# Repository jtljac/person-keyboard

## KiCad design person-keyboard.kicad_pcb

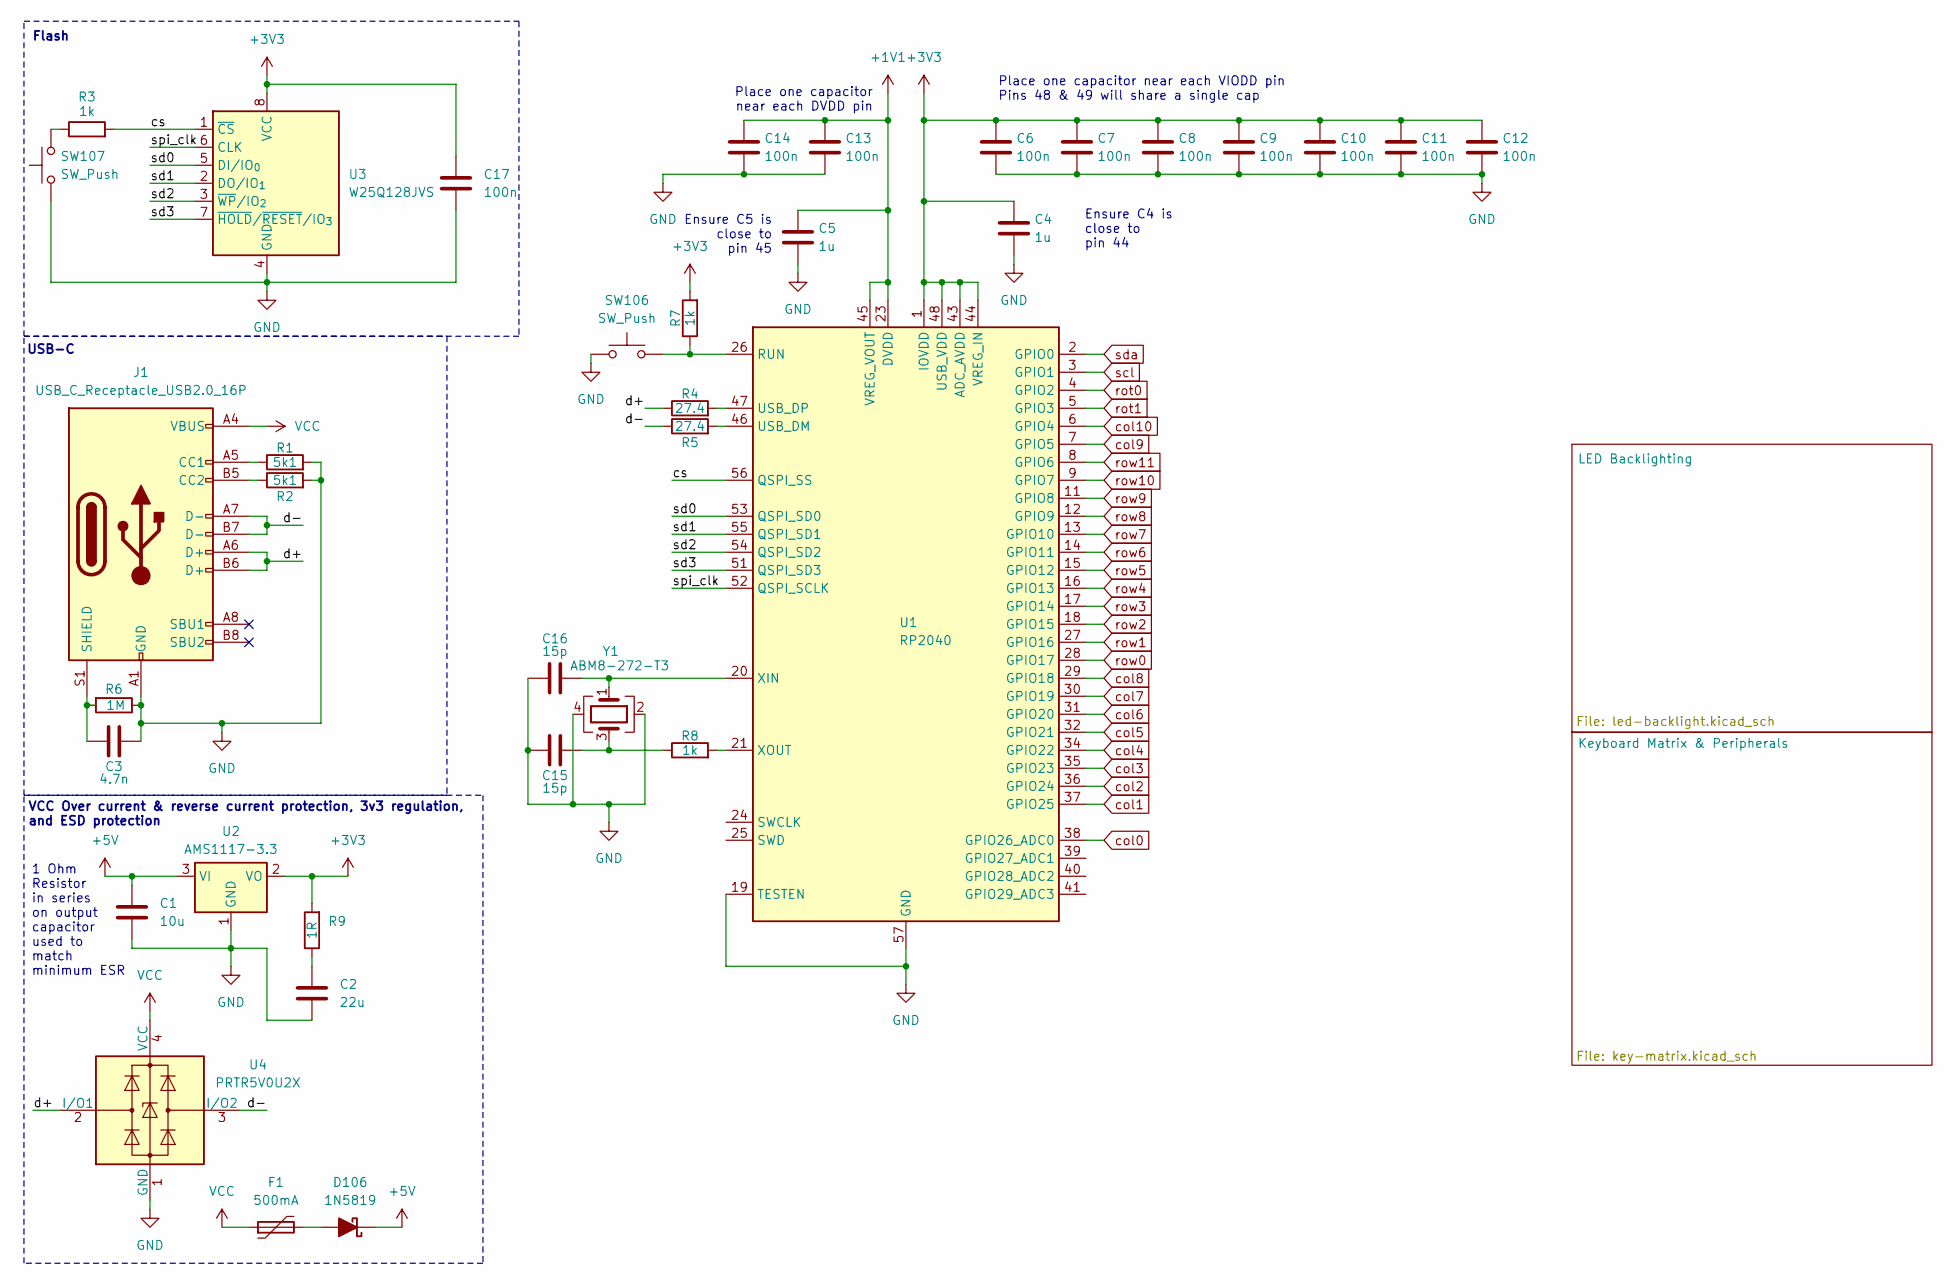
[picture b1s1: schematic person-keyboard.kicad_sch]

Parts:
C1: 10u; C_0805_2012Metric_Pad1.18x1.45mm_HandSolder
C2: 22u; C_0805_2012Metric_Pad1.18x1.45mm_HandSolder
C3: 4.7n; C_0805_2012Metric_Pad1.18x1.45mm_HandSolder
C4, C5: 1u; C_0402_1005Metric_Pad0.74x0.62mm_HandSolder
C6, C7, C8, C9, C10, C11, C12, C13, C14, C17: 100n; C_0402_1005Metric_Pad0.74x0.62mm_HandSolder
C15, C16: 15p; C_0402_1005Metric_Pad0.74x0.62mm_HandSolder
D106: 1N5819; D_SOD-123
F1: 500mA; Fuse_0805_2012Metric
J1: USB_C_Receptacle_USB2.0_16P; USB_C_Receptacle_GCT_USB4105-xx-A_16P_TopMnt_Horizontal
R1, R2: 5k1; R_0805_2012Metric_Pad1.20x1.40mm_HandSolder
R3: 1k; R_0805_2012Metric_Pad1.20x1.40mm_HandSolder
R4, R5: 27.4; R_0402_1005Metric_Pad0.72x0.64mm_HandSolder
R6: 1M; R_0805_2012Metric
R7, R8: 1k; R_0402_1005Metric_Pad0.72x0.64mm_HandSolder
R9: 1R; R_0805_2012Metric_Pad1.20x1.40mm_HandSolder
SW106, SW107: SW_Push; SW-SMD_L4.0-W2.9-LS5.0
U1: RP2040; QFN-56-1EP_7x7mm_P0.4mm_EP3.2x3.2mm_vias
U2: AMS1117-3.3; SOT-223-3_TabPin2
U3: W25Q128JVS; SOIC-8_5.3x5.3mm_P1.27mm
U4: PRTR5V0U2X; SOT-143
Y1: ABM8-272-T3; Crystal_SMD_3225-4Pin_3.2x2.5mm_HandSoldering

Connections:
+1V1: C5.1, C13.1, C14.1, U1.23 (DVDD), U1.45 (VREG_VOUT), U1.50 (DVDD)
+3V3: C4.1, C6.1, C7.1, C8.1, C9.1, C10.1, C11.1, C12.1, C17.1, R7.2, R9.2, U1.1 (IOVDD), U1.10 (IOVDD), U1.22 (IOVDD), U1.33 (IOVDD), U1.42 (IOVDD), U1.43 (ADC_AVDD), U1.44 (VREG_IN), U1.48 (USB_VDD), U1.49 (IOVDD), U2.2 (VO), U3.8 (VCC); also elsewhere on the board
+5V: C1.1, D106.1 (K), U2.3 (VI); also elsewhere on the board
/cs: R3.2, U1.56 (QSPI_SS), U3.1 (~CS)
/d+: J1.A6 (D+), J1.B6 (D+), R4.1, U4.2 (I/O1)
/d-: J1.A7 (D-), J1.B7 (D-), R5.1, U4.3 (I/O2)
/sd0: U1.53 (QSPI_SD0), U3.5 (DI/IO_{0})
/sd1: U1.55 (QSPI_SD1), U3.2 (DO/IO_{1})
/sd2: U1.54 (QSPI_SD2), U3.3 (~WP/IO_{2})
/sd3: U1.51 (QSPI_SD3), U3.7 (~HOLD/~RESET/IO_{3})
/spi_clk: U1.52 (QSPI_SCLK), U3.6 (CLK)
GND: C1.2, C2.2, C3.2, C4.2, C5.2, C6.2, C7.2, C8.2, C9.2, C10.2, C11.2, C12.2, C13.2, C14.2, C15.1, C16.1, C17.2, J1.A1 (GND), J1.A12 (GND), J1.B1 (GND), J1.B12 (GND), R1.2, R2.2, R6.1, SW106.1, SW107.1, U1.19 (TESTEN), U1.57 (GND), U2.1 (GND), U3.4 (GND), U4.1 (GND), Y1.2, Y1.4; also elsewhere on the board
unnamed: C2.1, R9.1
unnamed: C15.2, R8.1, Y1.3
unnamed: D106.2 (A), F1.2
unnamed: J1.A5 (CC1), R1.1
unnamed: J1.B5 (CC2), R2.1
unnamed: C3.1, J1.S1 (SHIELD), R6.2
unnamed: R3.1, SW107.2
unnamed: R7.1, SW106.2, U1.26 (RUN)
unnamed: R5.2, U1.46 (USB_DM)
unnamed: R4.2, U1.47 (USB_DP)
unnamed: C16.2, U1.20 (XIN), Y1.1
unnamed: R8.2, U1.21 (XOUT)
VCC: F1.1, J1.A4 (VBUS), J1.A9 (VBUS), J1.B4 (VBUS), J1.B9 (VBUS), U4.4 (VCC)
col0: U1.38 (GPIO26_ADC0); also elsewhere on the board
col1: U1.37 (GPIO25); also elsewhere on the board
col2: U1.36 (GPIO24); also elsewhere on the board
col3: U1.35 (GPIO23); also elsewhere on the board
col4: U1.34 (GPIO22); also elsewhere on the board
col5: U1.32 (GPIO21); also elsewhere on the board
col6: U1.31 (GPIO20); also elsewhere on the board
col7: U1.30 (GPIO19); also elsewhere on the board
col8: U1.29 (GPIO18); also elsewhere on the board
col9: U1.7 (GPIO5); also elsewhere on the board
col10: U1.6 (GPIO4); also elsewhere on the board
rot0: U1.4 (GPIO2); also elsewhere on the board
rot1: U1.5 (GPIO3); also elsewhere on the board
row0: U1.28 (GPIO17); also elsewhere on the board
row1: U1.27 (GPIO16); also elsewhere on the board
row2: U1.18 (GPIO15); also elsewhere on the board
row3: U1.17 (GPIO14); also elsewhere on the board
row4: U1.16 (GPIO13); also elsewhere on the board
row5: U1.15 (GPIO12); also elsewhere on the board
row6: U1.14 (GPIO11); also elsewhere on the board
row7: U1.13 (GPIO10); also elsewhere on the board
row8: U1.12 (GPIO9); also elsewhere on the board
row9: U1.11 (GPIO8); also elsewhere on the board
row10: U1.9 (GPIO7); also elsewhere on the board
row11: U1.8 (GPIO6); also elsewhere on the board
scl: U1.3 (GPIO1); also elsewhere on the board
sda: U1.2 (GPIO0); also elsewhere on the board

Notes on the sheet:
Place one capacitor near each DVDD pin
USB-C
VCC Over current & reverse current protection, 3v3 regulation, and ESD protection
1 Ohm Resistor in series on output capacitor used to match minimum ESR
Flash
Place one capacitor near each VIODD pin Pins 48 & 49 will share a single cap
Ensure C5 is close to pin 45
Ensure C4 is close to pin 44

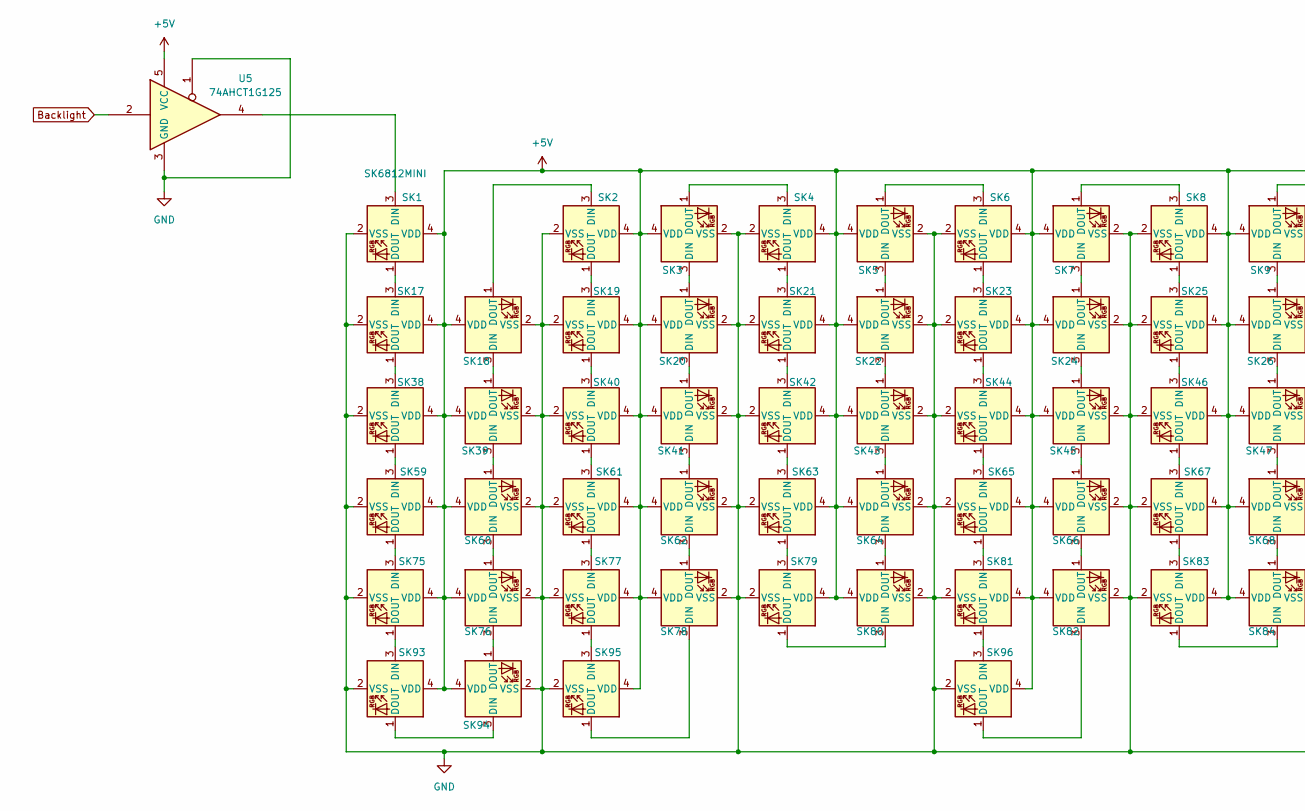
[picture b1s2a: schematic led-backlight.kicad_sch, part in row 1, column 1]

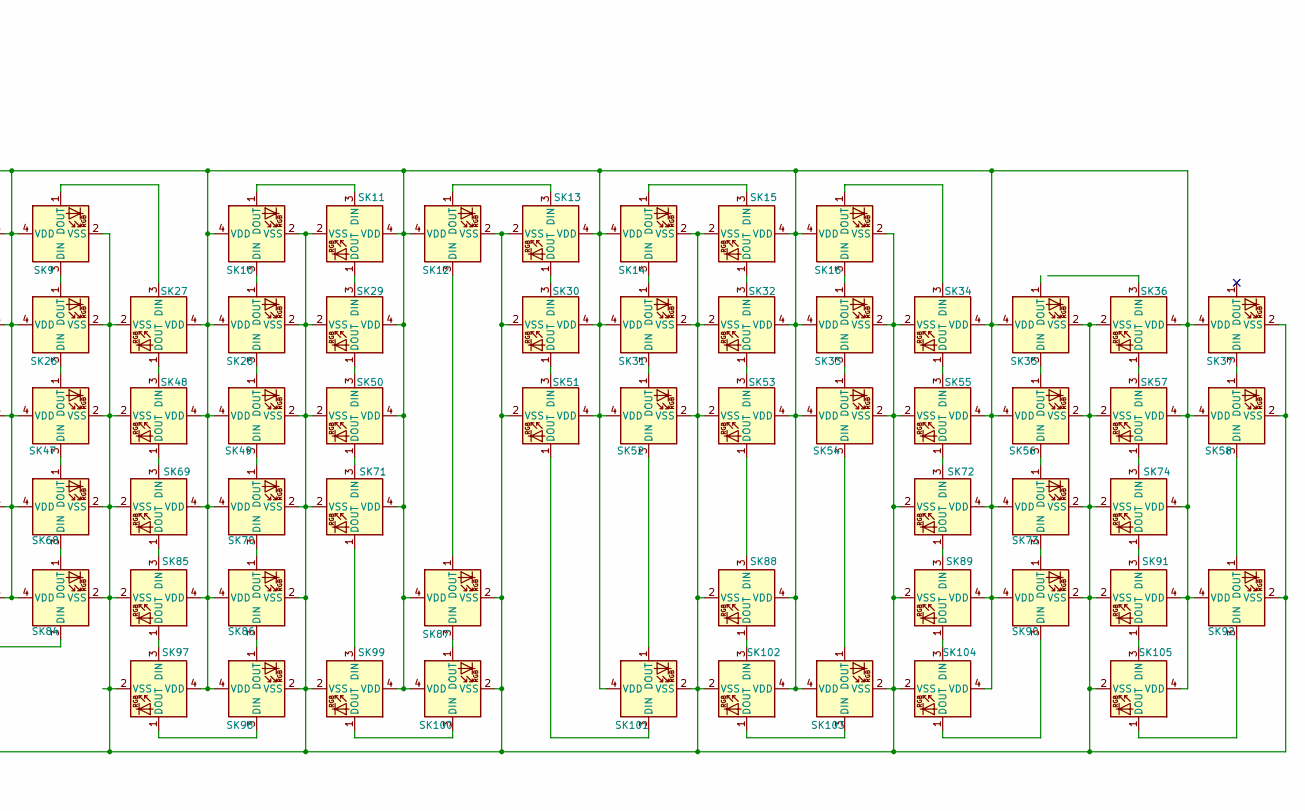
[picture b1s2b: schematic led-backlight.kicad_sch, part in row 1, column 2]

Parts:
SK1, SK2, SK3, SK4, SK5, SK6, SK7, SK8, SK9, SK10, SK11, SK12, SK13, SK14, SK15, SK16, SK17, SK18, SK19, SK20, SK21, SK22, SK23, SK24, SK25, SK26, SK27, SK28, SK29, SK30, SK31, SK32, SK33, SK34, SK35, SK36, SK37, SK38, SK39, SK40, SK41, SK42, SK43, SK44, SK45, SK46, SK47, SK48, SK49, SK50, SK51, SK52, SK53, SK54, SK55, SK56, SK57, SK58, SK59, SK60, SK61, SK62, SK63, SK64, SK65, SK66, SK67, SK68, SK69, SK70, SK71, SK72, SK73, SK74, SK75, SK76, SK77, SK78, SK79, SK80, SK81, SK82, SK83, SK84, SK85, SK86, SK87, SK88, SK89, SK90, SK91, SK92, SK93, SK94, SK95, SK96, SK97, SK98, SK99, SK100, SK101, SK102, SK103, SK104, SK105: SK6812MINI; SK6812-MINI-E
U5: 74AHCT1G125; SOT-23-5_HandSoldering

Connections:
+5V: SK1.4 (VDD), SK2.4 (VDD), SK3.4 (VDD), SK4.4 (VDD), SK5.4 (VDD), SK6.4 (VDD), SK7.4 (VDD), SK8.4 (VDD), SK9.4 (VDD), SK10.4 (VDD), SK11.4 (VDD), SK12.4 (VDD), SK13.4 (VDD), SK14.4 (VDD), SK15.4 (VDD), SK16.4 (VDD), SK17.4 (VDD), SK18.4 (VDD), SK19.4 (VDD), SK20.4 (VDD), SK21.4 (VDD), SK22.4 (VDD), SK23.4 (VDD), SK24.4 (VDD), SK25.4 (VDD), SK26.4 (VDD), SK27.4 (VDD), SK28.4 (VDD), SK29.4 (VDD), SK30.4 (VDD), SK31.4 (VDD), SK32.4 (VDD), SK33.4 (VDD), SK34.4 (VDD), SK35.4 (VDD), SK36.4 (VDD), SK37.4 (VDD), SK38.4 (VDD), SK39.4 (VDD), SK40.4 (VDD), SK41.4 (VDD), SK42.4 (VDD), SK43.4 (VDD), SK44.4 (VDD), SK45.4 (VDD), SK46.4 (VDD), SK47.4 (VDD), SK48.4 (VDD), SK49.4 (VDD), SK50.4 (VDD), SK51.4 (VDD), SK52.4 (VDD), SK53.4 (VDD), SK54.4 (VDD), SK55.4 (VDD), SK56.4 (VDD), SK57.4 (VDD), SK58.4 (VDD), SK59.4 (VDD), SK60.4 (VDD), SK61.4 (VDD), SK62.4 (VDD), SK63.4 (VDD), SK64.4 (VDD), SK65.4 (VDD), SK66.4 (VDD), SK67.4 (VDD), SK68.4 (VDD), SK69.4 (VDD), SK70.4 (VDD), SK71.4 (VDD), SK72.4 (VDD), SK73.4 (VDD), SK74.4 (VDD), SK75.4 (VDD), SK76.4 (VDD), SK77.4 (VDD), SK78.4 (VDD), SK79.4 (VDD), SK80.4 (VDD), SK81.4 (VDD), SK82.4 (VDD), SK83.4 (VDD), SK84.4 (VDD), SK85.4 (VDD), SK86.4 (VDD), SK87.4 (VDD), SK88.4 (VDD), SK89.4 (VDD), SK90.4 (VDD), SK91.4 (VDD), SK92.4 (VDD), SK93.4 (VDD), SK94.4 (VDD), SK95.4 (VDD), SK96.4 (VDD), SK97.4 (VDD), SK98.4 (VDD), SK99.4 (VDD), SK100.4 (VDD), SK101.4 (VDD), SK102.4 (VDD), SK103.4 (VDD), SK104.4 (VDD), SK105.4 (VDD), U5.5 (VCC); also elsewhere on the board
Backlight: U5.2
GND: SK1.2 (VSS), SK2.2 (VSS), SK3.2 (VSS), SK4.2 (VSS), SK5.2 (VSS), SK6.2 (VSS), SK7.2 (VSS), SK8.2 (VSS), SK9.2 (VSS), SK10.2 (VSS), SK11.2 (VSS), SK12.2 (VSS), SK13.2 (VSS), SK14.2 (VSS), SK15.2 (VSS), SK16.2 (VSS), SK17.2 (VSS), SK18.2 (VSS), SK19.2 (VSS), SK20.2 (VSS), SK21.2 (VSS), SK22.2 (VSS), SK23.2 (VSS), SK24.2 (VSS), SK25.2 (VSS), SK26.2 (VSS), SK27.2 (VSS), SK28.2 (VSS), SK29.2 (VSS), SK30.2 (VSS), SK31.2 (VSS), SK32.2 (VSS), SK33.2 (VSS), SK34.2 (VSS), SK35.2 (VSS), SK36.2 (VSS), SK37.2 (VSS), SK38.2 (VSS), SK39.2 (VSS), SK40.2 (VSS), SK41.2 (VSS), SK42.2 (VSS), SK43.2 (VSS), SK44.2 (VSS), SK45.2 (VSS), SK46.2 (VSS), SK47.2 (VSS), SK48.2 (VSS), SK49.2 (VSS), SK50.2 (VSS), SK51.2 (VSS), SK52.2 (VSS), SK53.2 (VSS), SK54.2 (VSS), SK55.2 (VSS), SK56.2 (VSS), SK57.2 (VSS), SK58.2 (VSS), SK59.2 (VSS), SK60.2 (VSS), SK61.2 (VSS), SK62.2 (VSS), SK63.2 (VSS), SK64.2 (VSS), SK65.2 (VSS), SK66.2 (VSS), SK67.2 (VSS), SK68.2 (VSS), SK69.2 (VSS), SK70.2 (VSS), SK71.2 (VSS), SK72.2 (VSS), SK73.2 (VSS), SK74.2 (VSS), SK75.2 (VSS), SK76.2 (VSS), SK77.2 (VSS), SK78.2 (VSS), SK79.2 (VSS), SK80.2 (VSS), SK81.2 (VSS), SK82.2 (VSS), SK83.2 (VSS), SK84.2 (VSS), SK85.2 (VSS), SK86.2 (VSS), SK87.2 (VSS), SK88.2 (VSS), SK89.2 (VSS), SK90.2 (VSS), SK91.2 (VSS), SK92.2 (VSS), SK93.2 (VSS), SK94.2 (VSS), SK95.2 (VSS), SK96.2 (VSS), SK97.2 (VSS), SK98.2 (VSS), SK99.2 (VSS), SK100.2 (VSS), SK101.2 (VSS), SK102.2 (VSS), SK103.2 (VSS), SK104.2 (VSS), SK105.2 (VSS), U5.1, U5.3 (GND); also elsewhere on the board
unnamed: SK1.3 (DIN), U5.4
unnamed: SK1.1 (DOUT), SK17.3 (DIN)
unnamed: SK3.1 (DOUT), SK4.3 (DIN)
unnamed: SK5.1 (DOUT), SK6.3 (DIN)
unnamed: SK7.1 (DOUT), SK8.3 (DIN)
unnamed: SK10.3 (DIN), SK28.1 (DOUT)
unnamed: SK10.1 (DOUT), SK11.3 (DIN)
unnamed: SK11.1 (DOUT), SK29.3 (DIN)
unnamed: SK12.3 (DIN), SK87.1 (DOUT)
unnamed: SK12.1 (DOUT), SK13.3 (DIN)
unnamed: SK13.1 (DOUT), SK30.3 (DIN)
unnamed: SK14.3 (DIN), SK31.1 (DOUT)
unnamed: SK14.1 (DOUT), SK15.3 (DIN)
unnamed: SK15.1 (DOUT), SK32.3 (DIN)
unnamed: SK16.3 (DIN), SK33.1 (DOUT)
unnamed: SK16.1 (DOUT), SK34.3 (DIN)
unnamed: SK17.1 (DOUT), SK38.3 (DIN)
unnamed: SK18.3 (DIN), SK39.1 (DOUT)
unnamed: SK2.3 (DIN), SK18.1 (DOUT)
unnamed: SK2.1 (DOUT), SK19.3 (DIN)
unnamed: SK19.1 (DOUT), SK40.3 (DIN)
unnamed: SK20.3 (DIN), SK41.1 (DOUT)
unnamed: SK3.3 (DIN), SK20.1 (DOUT)
unnamed: SK4.1 (DOUT), SK21.3 (DIN)
unnamed: SK21.1 (DOUT), SK42.3 (DIN)
unnamed: SK22.3 (DIN), SK43.1 (DOUT)
unnamed: SK5.3 (DIN), SK22.1 (DOUT)
unnamed: SK6.1 (DOUT), SK23.3 (DIN)
unnamed: SK23.1 (DOUT), SK44.3 (DIN)
unnamed: SK24.3 (DIN), SK45.1 (DOUT)
unnamed: SK7.3 (DIN), SK24.1 (DOUT)
unnamed: SK8.1 (DOUT), SK25.3 (DIN)
unnamed: SK25.1 (DOUT), SK46.3 (DIN)
unnamed: SK26.3 (DIN), SK47.1 (DOUT)
unnamed: SK9.3 (DIN), SK26.1 (DOUT)
unnamed: SK9.1 (DOUT), SK27.3 (DIN)
unnamed: SK27.1 (DOUT), SK48.3 (DIN)
unnamed: SK28.3 (DIN), SK49.1 (DOUT)
unnamed: SK29.1 (DOUT), SK50.3 (DIN)
unnamed: SK30.1 (DOUT), SK51.3 (DIN)
unnamed: SK31.3 (DIN), SK52.1 (DOUT)
unnamed: SK32.1 (DOUT), SK53.3 (DIN)
unnamed: SK33.3 (DIN), SK54.1 (DOUT)
unnamed: SK34.1 (DOUT), SK55.3 (DIN)
unnamed: SK35.3 (DIN), SK56.1 (DOUT)
unnamed: SK36.1 (DOUT), SK57.3 (DIN)
unnamed: SK37.3 (DIN), SK58.1 (DOUT)
unnamed: SK38.1 (DOUT), SK59.3 (DIN)
unnamed: SK39.3 (DIN), SK60.1 (DOUT)
unnamed: SK40.1 (DOUT), SK61.3 (DIN)
unnamed: SK41.3 (DIN), SK62.1 (DOUT)
unnamed: SK42.1 (DOUT), SK63.3 (DIN)
unnamed: SK43.3 (DIN), SK64.1 (DOUT)
unnamed: SK44.1 (DOUT), SK65.3 (DIN)
unnamed: SK45.3 (DIN), SK66.1 (DOUT)
unnamed: SK46.1 (DOUT), SK67.3 (DIN)
unnamed: SK47.3 (DIN), SK68.1 (DOUT)
unnamed: SK48.1 (DOUT), SK69.3 (DIN)
unnamed: SK49.3 (DIN), SK70.1 (DOUT)
unnamed: SK50.1 (DOUT), SK71.3 (DIN)
unnamed: SK53.1 (DOUT), SK88.3 (DIN)
unnamed: SK55.1 (DOUT), SK72.3 (DIN)
unnamed: SK56.3 (DIN), SK73.1 (DOUT)
unnamed: SK57.1 (DOUT), SK74.3 (DIN)
unnamed: SK58.3 (DIN), SK92.1 (DOUT)
unnamed: SK59.1 (DOUT), SK75.3 (DIN)
unnamed: SK60.3 (DIN), SK76.1 (DOUT)
unnamed: SK61.1 (DOUT), SK77.3 (DIN)
unnamed: SK62.3 (DIN), SK78.1 (DOUT)
unnamed: SK63.1 (DOUT), SK79.3 (DIN)
unnamed: SK64.3 (DIN), SK80.1 (DOUT)
unnamed: SK65.1 (DOUT), SK81.3 (DIN)
unnamed: SK66.3 (DIN), SK82.1 (DOUT)
unnamed: SK67.1 (DOUT), SK83.3 (DIN)
unnamed: SK68.3 (DIN), SK84.1 (DOUT)
unnamed: SK69.1 (DOUT), SK85.3 (DIN)
unnamed: SK70.3 (DIN), SK86.1 (DOUT)
unnamed: SK71.1 (DOUT), SK99.3 (DIN)
unnamed: SK72.1 (DOUT), SK89.3 (DIN)
unnamed: SK73.3 (DIN), SK90.1 (DOUT)
unnamed: SK74.1 (DOUT), SK91.3 (DIN)
unnamed: SK75.1 (DOUT), SK93.3 (DIN)
unnamed: SK76.3 (DIN), SK94.1 (DOUT)
unnamed: SK77.1 (DOUT), SK95.3 (DIN)
unnamed: SK78.3 (DIN), SK95.1 (DOUT)
unnamed: SK79.1 (DOUT), SK80.3 (DIN)
unnamed: SK81.1 (DOUT), SK96.3 (DIN)
unnamed: SK82.3 (DIN), SK96.1 (DOUT)
unnamed: SK83.1 (DOUT), SK84.3 (DIN)
unnamed: SK85.1 (DOUT), SK97.3 (DIN)
unnamed: SK86.3 (DIN), SK98.1 (DOUT)
unnamed: SK93.1 (DOUT), SK94.3 (DIN)
unnamed: SK97.1 (DOUT), SK98.3 (DIN)
unnamed: SK99.1 (DOUT), SK100.3 (DIN)
unnamed: SK87.3 (DIN), SK100.1 (DOUT)
unnamed: SK51.1 (DOUT), SK101.3 (DIN)
unnamed: SK52.3 (DIN), SK101.1 (DOUT)
unnamed: SK88.1 (DOUT), SK102.3 (DIN)
unnamed: SK102.1 (DOUT), SK103.3 (DIN)
unnamed: SK54.3 (DIN), SK103.1 (DOUT)
unnamed: SK89.1 (DOUT), SK104.3 (DIN)
unnamed: SK90.3 (DIN), SK104.1 (DOUT)
unnamed: SK91.1 (DOUT), SK105.3 (DIN)
unnamed: SK92.3 (DIN), SK105.1 (DOUT)

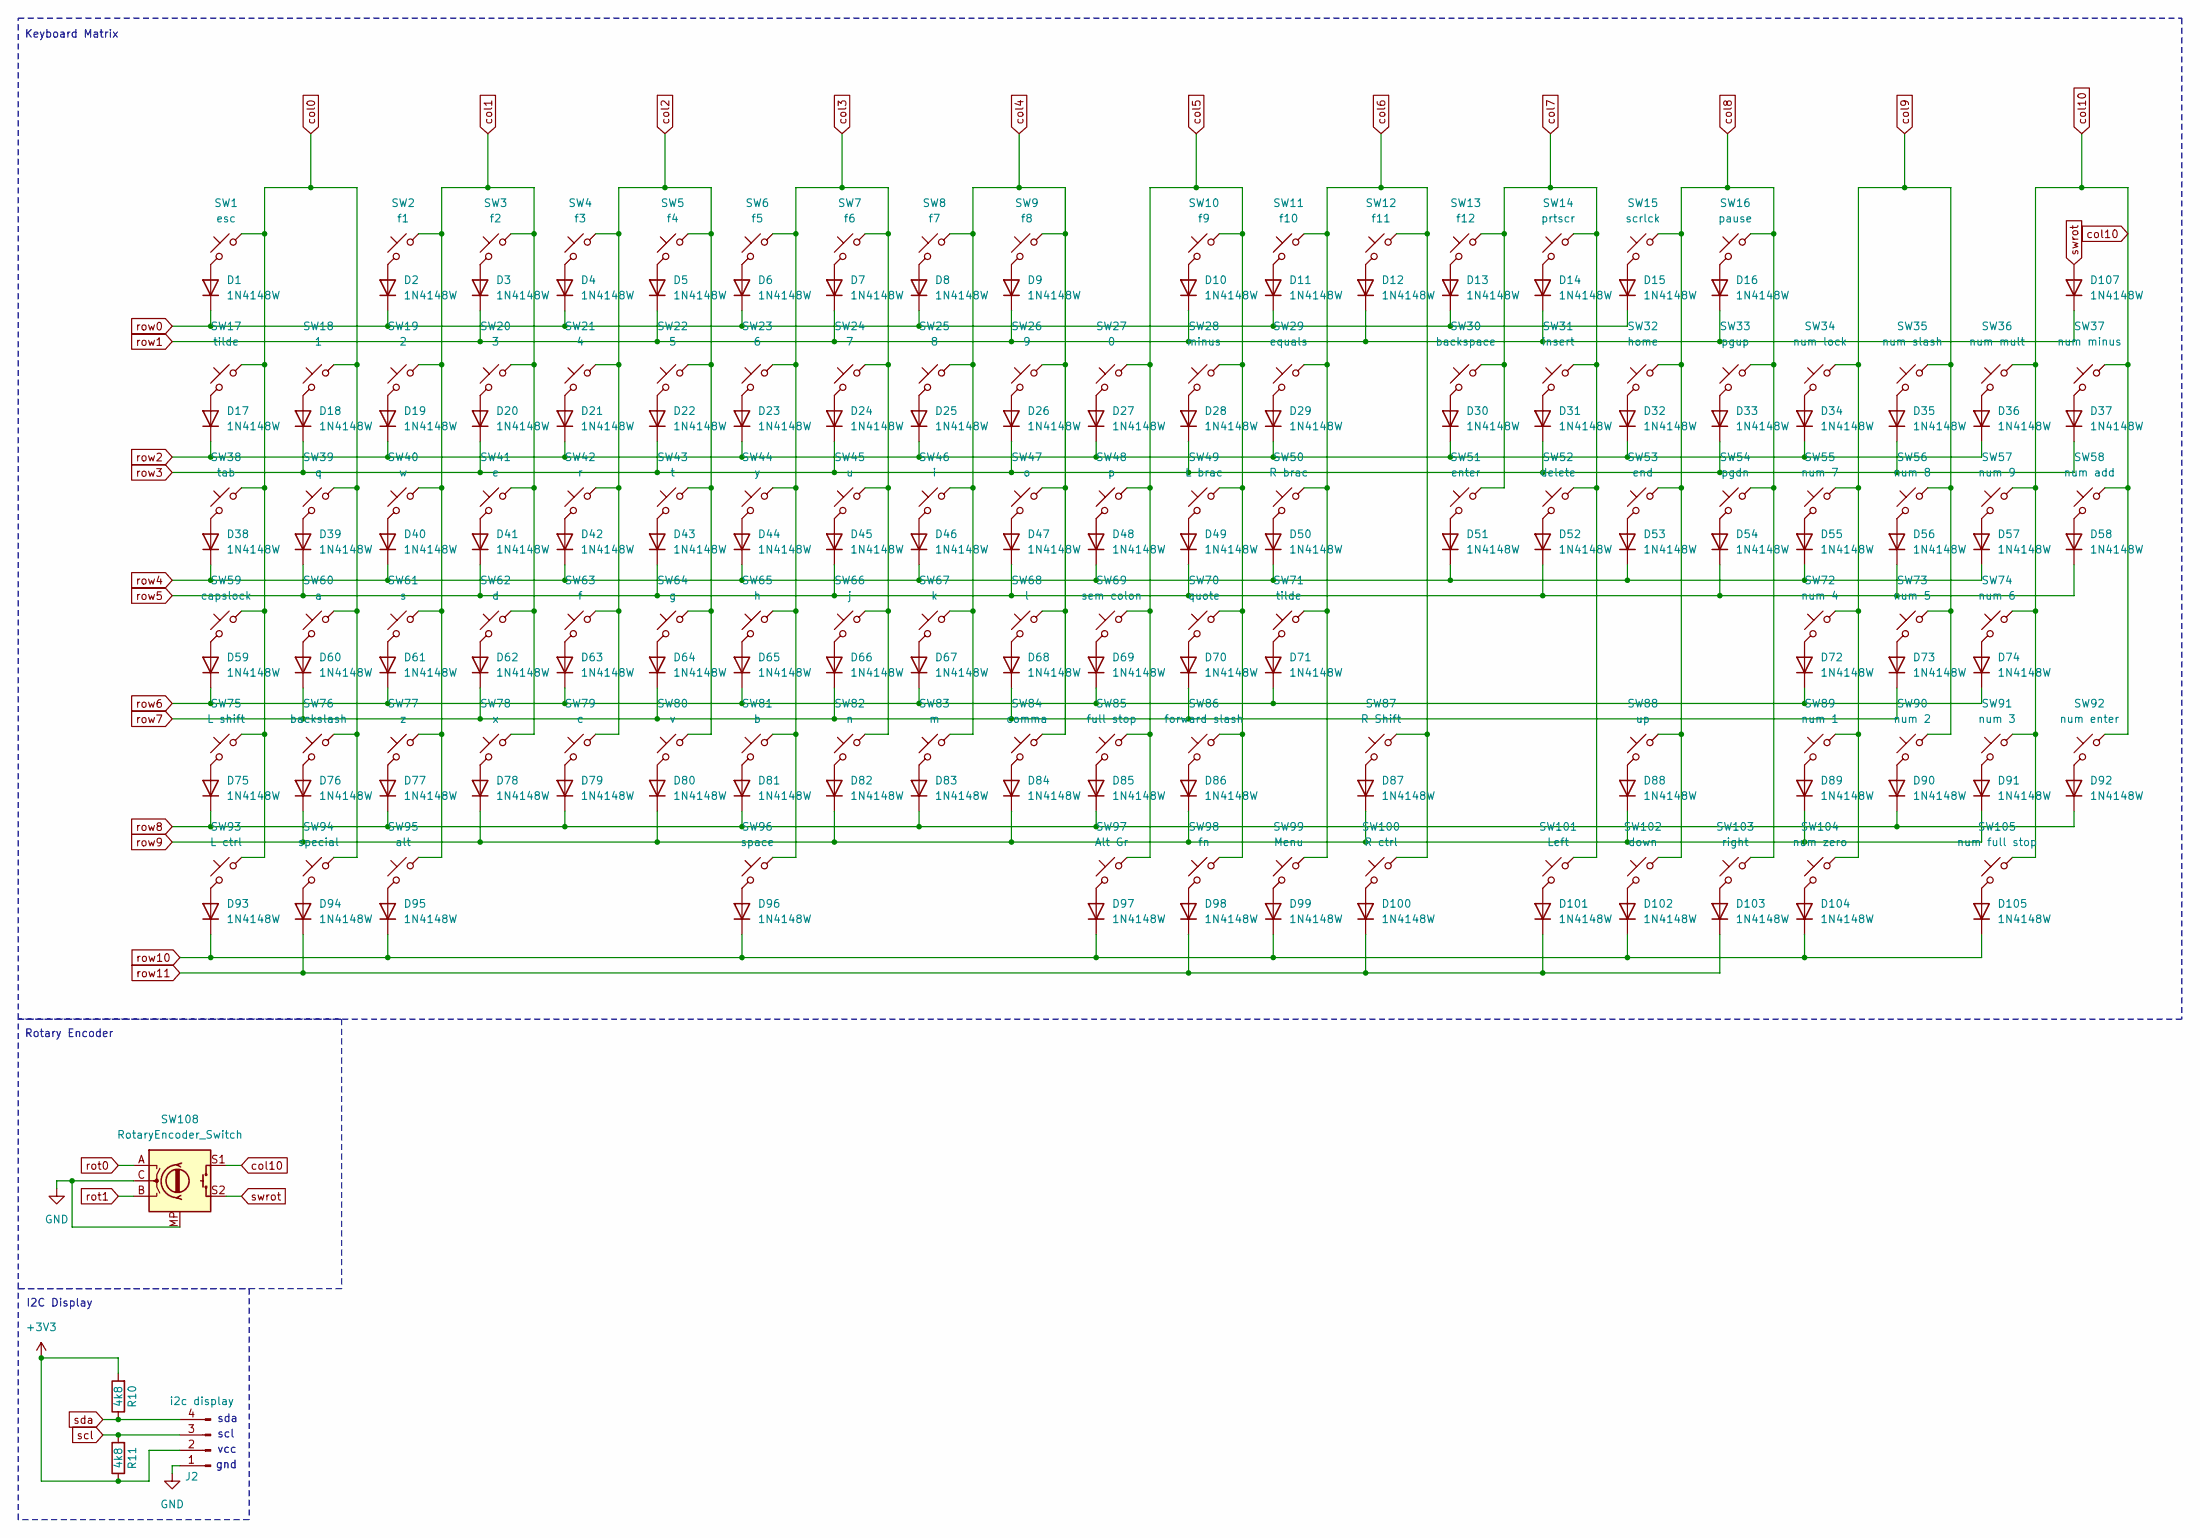
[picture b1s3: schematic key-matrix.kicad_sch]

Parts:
D1, D2, D3, D4, D5, D6, D7, D8, D9, D10, D11, D12, D13, D14, D15, D16, D17, D18, D19, D20, D21, D22, D23, D24, D25, D26, D27, D28, D29, D30, D31, D32, D33, D34, D35, D36, D37, D38, D39, D40, D41, D42, D43, D44, D45, D46, D47, D48, D49, D50, D51, D52, D53, D54, D55, D56, D57, D58, D59, D60, D61, D62, D63, D64, D65, D66, D67, D68, D69, D70, D71, D72, D73, D74, D75, D76, D77, D78, D79, D80, D81, D82, D83, D84, D85, D86, D87, D88, D89, D90, D91, D92, D93, D94, D95, D96, D97, D98, D99, D100, D101, D102, D103, D104, D105, D107: 1N4148W; D_SOD-123
J2: i2c display; 0.91 OLED I2C DISPLAY
R10, R11: 4k8; R_0805_2012Metric_Pad1.20x1.40mm_HandSolder
SW1: esc; Gateron-KS33-Hotswap-1U
SW2: f1; Gateron-KS33-Hotswap-1U
SW3: f2; Gateron-KS33-Hotswap-1U
SW4: f3; Gateron-KS33-Hotswap-1U
SW5: f4; Gateron-KS33-Hotswap-1U
SW6: f5; Gateron-KS33-Hotswap-1U
SW7: f6; Gateron-KS33-Hotswap-1U
SW8: f7; Gateron-KS33-Hotswap-1U
SW9: f8; Gateron-KS33-Hotswap-1U
SW10: f9; Gateron-KS33-Hotswap-1U
SW11: f10; Gateron-KS33-Hotswap-1U
SW12: f11; Gateron-KS33-Hotswap-1U
SW13: f12; Gateron-KS33-Hotswap-1U
SW14: prtscr; Gateron-KS33-Hotswap-1U
SW15: scrlck; Gateron-KS33-Hotswap-1U
SW16: pause; Gateron-KS33-Hotswap-1U
SW17, SW71: tilde; Gateron-KS33-Hotswap-1U
SW18: 1; Gateron-KS33-Hotswap-1U
SW19: 2; Gateron-KS33-Hotswap-1U
SW20: 3; Gateron-KS33-Hotswap-1U
SW21: 4; Gateron-KS33-Hotswap-1U
SW22: 5; Gateron-KS33-Hotswap-1U
SW23: 6; Gateron-KS33-Hotswap-1U
SW24: 7; Gateron-KS33-Hotswap-1U
SW25: 8; Gateron-KS33-Hotswap-1U
SW26: 9; Gateron-KS33-Hotswap-1U
SW27: 0; Gateron-KS33-Hotswap-1U
SW28: minus; Gateron-KS33-Hotswap-1U
SW29: equals; Gateron-KS33-Hotswap-1U
SW30: backspace; Gateron-KS33-Hotswap-2U
SW31: insert; Gateron-KS33-Hotswap-1U
SW32: home; Gateron-KS33-Hotswap-1U
SW33: pgup; Gateron-KS33-Hotswap-1U
SW34: num lock; Gateron-KS33-Hotswap-1U
SW35: num slash; Gateron-KS33-Hotswap-1U
SW36: num mult; Gateron-KS33-Hotswap-1U
SW37: num minus; Gateron-KS33-Hotswap-1U
SW38: tab; Gateron-KS33-Hotswap-1.5U
SW39: q; Gateron-KS33-Hotswap-1U
SW40: w; Gateron-KS33-Hotswap-1U
SW41: e; Gateron-KS33-Hotswap-1U
SW42: r; Gateron-KS33-Hotswap-1U
SW43: t; Gateron-KS33-Hotswap-1U
SW44: y; Gateron-KS33-Hotswap-1U
SW45: u; Gateron-KS33-Hotswap-1U
SW46: i; Gateron-KS33-Hotswap-1U
SW47: o; Gateron-KS33-Hotswap-1U
SW48: p; Gateron-KS33-Hotswap-1U
SW49: L brac; Gateron-KS33-Hotswap-1U
SW50: R brac; Gateron-KS33-Hotswap-1U
SW51: enter; Gateron-KS33-Hotswap-2U-90-Deg
SW52: delete; Gateron-KS33-Hotswap-1U
SW53: end; Gateron-KS33-Hotswap-1U
SW54: pgdn; Gateron-KS33-Hotswap-1U
SW55: num 7; Gateron-KS33-Hotswap-1U
SW56: num 8; Gateron-KS33-Hotswap-1U
SW57: num 9; Gateron-KS33-Hotswap-1U
SW58: num add; Gateron-KS33-Hotswap-2U-90-Deg
SW59: capslock; Gateron-KS33-Hotswap-1.75U
SW60: a; Gateron-KS33-Hotswap-1U
SW61: s; Gateron-KS33-Hotswap-1U
SW62: d; Gateron-KS33-Hotswap-1U
SW63: f; Gateron-KS33-Hotswap-1U
SW64: g; Gateron-KS33-Hotswap-1U
SW65: h; Gateron-KS33-Hotswap-1U
SW66: j; Gateron-KS33-Hotswap-1U
SW67: k; Gateron-KS33-Hotswap-1U
SW68: l; Gateron-KS33-Hotswap-1U
SW69: sem colon; Gateron-KS33-Hotswap-1U
SW70: quote; Gateron-KS33-Hotswap-1U
SW72: num 4; Gateron-KS33-Hotswap-1U
SW73: num 5; Gateron-KS33-Hotswap-1U
SW74: num 6; Gateron-KS33-Hotswap-1U
SW75: L shift; Gateron-KS33-Hotswap-1.25U
SW76: backslash; Gateron-KS33-Hotswap-1U
SW77: z; Gateron-KS33-Hotswap-1U
SW78: x; Gateron-KS33-Hotswap-1U
SW79: c; Gateron-KS33-Hotswap-1U
SW80: v; Gateron-KS33-Hotswap-1U
SW81: b; Gateron-KS33-Hotswap-1U
SW82: n; Gateron-KS33-Hotswap-1U
SW83: m; Gateron-KS33-Hotswap-1U
SW84: comma; Gateron-KS33-Hotswap-1U
SW85: full stop; Gateron-KS33-Hotswap-1U
SW86: forward slash; Gateron-KS33-Hotswap-1U
SW87: R Shift; Gateron-KS33-Hotswap-2.75U
SW88: up; Gateron-KS33-Hotswap-1U
SW89: num 1; Gateron-KS33-Hotswap-1U
SW90: num 2; Gateron-KS33-Hotswap-1U
SW91: num 3; Gateron-KS33-Hotswap-1U
SW92: num enter; Gateron-KS33-Hotswap-2U-90-Deg
SW93: L ctrl; Gateron-KS33-Hotswap-1.25U
SW94: special; Gateron-KS33-Hotswap-1.25U
SW95: alt; Gateron-KS33-Hotswap-1.25U
SW96: space; Gateron-KS33-Hotswap-6.25U
SW97: Alt Gr; Gateron-KS33-Hotswap-1.25U
SW98: fn; Gateron-KS33-Hotswap-1.25U
SW99: Menu; Gateron-KS33-Hotswap-1.25U
SW100: R ctrl; Gateron-KS33-Hotswap-1.25U
SW101: Left; Gateron-KS33-Hotswap-1U
SW102: down; Gateron-KS33-Hotswap-1U
SW103: right; Gateron-KS33-Hotswap-1U
SW104: num zero; Gateron-KS33-Hotswap-2U
SW105: num full stop; Gateron-KS33-Hotswap-1U
SW108: RotaryEncoder_Switch; RotaryEncoder_Alps_EC11E-Switch_Vertical_H20mm

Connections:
+3V3: J2.2, R10.2, R11.1; also elsewhere on the board
GND: J2.1, SW108.C, SW108.MP; also elsewhere on the board
unnamed: D1.2 (A), SW1.2
unnamed: D2.2 (A), SW2.2
unnamed: D3.2 (A), SW3.2
unnamed: D4.2 (A), SW4.2
unnamed: D5.2 (A), SW5.2
unnamed: D6.2 (A), SW6.2
unnamed: D7.2 (A), SW7.2
unnamed: D8.2 (A), SW8.2
unnamed: D9.2 (A), SW9.2
unnamed: D10.2 (A), SW10.2
unnamed: D11.2 (A), SW11.2
unnamed: D12.2 (A), SW12.2
unnamed: D13.2 (A), SW13.2
unnamed: D14.2 (A), SW14.2
unnamed: D15.2 (A), SW15.2
unnamed: D16.2 (A), SW16.2
unnamed: D17.2 (A), SW17.2
unnamed: D18.2 (A), SW18.2
unnamed: D19.2 (A), SW19.2
unnamed: D20.2 (A), SW20.2
unnamed: D21.2 (A), SW21.2
unnamed: D22.2 (A), SW22.2
unnamed: D23.2 (A), SW23.2
unnamed: D24.2 (A), SW24.2
unnamed: D25.2 (A), SW25.2
unnamed: D26.2 (A), SW26.2
unnamed: D27.2 (A), SW27.2
unnamed: D28.2 (A), SW28.2
unnamed: D29.2 (A), SW29.2
unnamed: D30.2 (A), SW30.2
unnamed: D31.2 (A), SW31.2
unnamed: D32.2 (A), SW32.2
unnamed: D33.2 (A), SW33.2
unnamed: D34.2 (A), SW34.2
unnamed: D35.2 (A), SW35.2
unnamed: D36.2 (A), SW36.2
unnamed: D37.2 (A), SW37.2
unnamed: D38.2 (A), SW38.2
unnamed: D39.2 (A), SW39.2
unnamed: D40.2 (A), SW40.2
unnamed: D41.2 (A), SW41.2
unnamed: D42.2 (A), SW42.2
unnamed: D43.2 (A), SW43.2
unnamed: D44.2 (A), SW44.2
unnamed: D45.2 (A), SW45.2
unnamed: D46.2 (A), SW46.2
unnamed: D47.2 (A), SW47.2
unnamed: D48.2 (A), SW48.2
unnamed: D49.2 (A), SW49.2
unnamed: D50.2 (A), SW50.2
unnamed: D51.2 (A), SW51.2
unnamed: D52.2 (A), SW52.2
unnamed: D53.2 (A), SW53.2
unnamed: D54.2 (A), SW54.2
unnamed: D55.2 (A), SW55.2
unnamed: D56.2 (A), SW56.2
unnamed: D57.2 (A), SW57.2
unnamed: D58.2 (A), SW58.2
unnamed: D59.2 (A), SW59.2
unnamed: D60.2 (A), SW60.2
unnamed: D61.2 (A), SW61.2
unnamed: D62.2 (A), SW62.2
unnamed: D63.2 (A), SW63.2
unnamed: D64.2 (A), SW64.2
unnamed: D65.2 (A), SW65.2
unnamed: D66.2 (A), SW66.2
unnamed: D67.2 (A), SW67.2
unnamed: D68.2 (A), SW68.2
unnamed: D69.2 (A), SW69.2
unnamed: D70.2 (A), SW70.2
unnamed: D71.2 (A), SW71.2
unnamed: D72.2 (A), SW72.2
unnamed: D73.2 (A), SW73.2
unnamed: D74.2 (A), SW74.2
unnamed: D75.2 (A), SW75.2
unnamed: D76.2 (A), SW76.2
unnamed: D77.2 (A), SW77.2
unnamed: D78.2 (A), SW78.2
unnamed: D79.2 (A), SW79.2
unnamed: D80.2 (A), SW80.2
unnamed: D81.2 (A), SW81.2
unnamed: D82.2 (A), SW82.2
unnamed: D83.2 (A), SW83.2
unnamed: D84.2 (A), SW84.2
unnamed: D85.2 (A), SW85.2
unnamed: D86.2 (A), SW86.2
unnamed: D87.2 (A), SW87.2
unnamed: D88.2 (A), SW88.2
unnamed: D89.2 (A), SW89.2
unnamed: D90.2 (A), SW90.2
unnamed: D91.2 (A), SW91.2
unnamed: D92.2 (A), SW92.2
unnamed: D93.2 (A), SW93.2
unnamed: D94.2 (A), SW94.2
unnamed: D95.2 (A), SW95.2
unnamed: D96.2 (A), SW96.2
unnamed: D97.2 (A), SW97.2
unnamed: D98.2 (A), SW98.2
unnamed: D99.2 (A), SW99.2
unnamed: D100.2 (A), SW100.2
unnamed: D101.2 (A), SW101.2
unnamed: D102.2 (A), SW102.2
unnamed: D103.2 (A), SW103.2
unnamed: D104.2 (A), SW104.2
unnamed: D105.2 (A), SW105.2
col0: SW1.1, SW17.1, SW18.1, SW38.1, SW39.1, SW59.1, SW60.1, SW75.1, SW76.1, SW93.1, SW94.1; also elsewhere on the board
col1: SW2.1, SW3.1, SW19.1, SW20.1, SW40.1, SW41.1, SW61.1, SW62.1, SW77.1, SW78.1, SW95.1; also elsewhere on the board
col2: SW4.1, SW5.1, SW21.1, SW22.1, SW42.1, SW43.1, SW63.1, SW64.1, SW79.1, SW80.1; also elsewhere on the board
col3: SW6.1, SW7.1, SW23.1, SW24.1, SW44.1, SW45.1, SW65.1, SW66.1, SW81.1, SW82.1, SW96.1; also elsewhere on the board
col4: SW8.1, SW9.1, SW25.1, SW26.1, SW46.1, SW47.1, SW67.1, SW68.1, SW83.1, SW84.1; also elsewhere on the board
col5: SW10.1, SW27.1, SW28.1, SW48.1, SW49.1, SW69.1, SW70.1, SW85.1, SW86.1, SW97.1, SW98.1; also elsewhere on the board
col6: SW11.1, SW12.1, SW29.1, SW50.1, SW71.1, SW87.1, SW99.1, SW100.1; also elsewhere on the board
col7: SW13.1, SW14.1, SW30.1, SW31.1, SW51.1, SW52.1, SW101.1; also elsewhere on the board
col8: SW15.1, SW16.1, SW32.1, SW33.1, SW53.1, SW54.1, SW88.1, SW102.1, SW103.1; also elsewhere on the board
col9: SW34.1, SW35.1, SW55.1, SW56.1, SW72.1, SW73.1, SW89.1, SW90.1, SW104.1; also elsewhere on the board
col10: SW36.1, SW37.1, SW57.1, SW58.1, SW74.1, SW91.1, SW92.1, SW105.1, SW108.S1; also elsewhere on the board
rot0: SW108.A; also elsewhere on the board
rot1: SW108.B; also elsewhere on the board
row0: D1.1 (K), D2.1 (K), D4.1 (K), D6.1 (K), D8.1 (K), D11.1 (K), D13.1 (K), D15.1 (K); also elsewhere on the board
row1: D3.1 (K), D5.1 (K), D7.1 (K), D9.1 (K), D10.1 (K), D12.1 (K), D14.1 (K), D16.1 (K), D107.1 (K); also elsewhere on the board
row2: D17.1 (K), D19.1 (K), D21.1 (K), D23.1 (K), D25.1 (K), D27.1 (K), D29.1 (K), D30.1 (K), D32.1 (K), D34.1 (K), D36.1 (K); also elsewhere on the board
row3: D18.1 (K), D20.1 (K), D22.1 (K), D24.1 (K), D26.1 (K), D28.1 (K), D31.1 (K), D33.1 (K), D35.1 (K), D37.1 (K); also elsewhere on the board
row4: D38.1 (K), D40.1 (K), D42.1 (K), D44.1 (K), D46.1 (K), D48.1 (K), D50.1 (K), D51.1 (K), D53.1 (K), D55.1 (K), D57.1 (K); also elsewhere on the board
row5: D39.1 (K), D41.1 (K), D43.1 (K), D45.1 (K), D47.1 (K), D49.1 (K), D52.1 (K), D54.1 (K), D56.1 (K), D58.1 (K); also elsewhere on the board
row6: D59.1 (K), D61.1 (K), D63.1 (K), D65.1 (K), D67.1 (K), D69.1 (K), D71.1 (K), D72.1 (K), D74.1 (K); also elsewhere on the board
row7: D60.1 (K), D62.1 (K), D64.1 (K), D66.1 (K), D68.1 (K), D70.1 (K), D73.1 (K); also elsewhere on the board
row8: D75.1 (K), D77.1 (K), D79.1 (K), D81.1 (K), D83.1 (K), D85.1 (K), D90.1 (K), D92.1 (K); also elsewhere on the board
row9: D76.1 (K), D78.1 (K), D80.1 (K), D82.1 (K), D84.1 (K), D86.1 (K), D87.1 (K), D88.1 (K), D89.1 (K), D91.1 (K); also elsewhere on the board
row10: D93.1 (K), D95.1 (K), D96.1 (K), D97.1 (K), D99.1 (K), D102.1 (K), D104.1 (K), D105.1 (K); also elsewhere on the board
row11: D94.1 (K), D98.1 (K), D100.1 (K), D101.1 (K), D103.1 (K); also elsewhere on the board
scl: J2.3, R11.2; also elsewhere on the board
sda: J2.4, R10.1; also elsewhere on the board
swrot: D107.2 (A), SW108.S2

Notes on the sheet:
scl
I2C Display
Rotary Encoder
sda
gnd
Keyboard Matrix
vcc

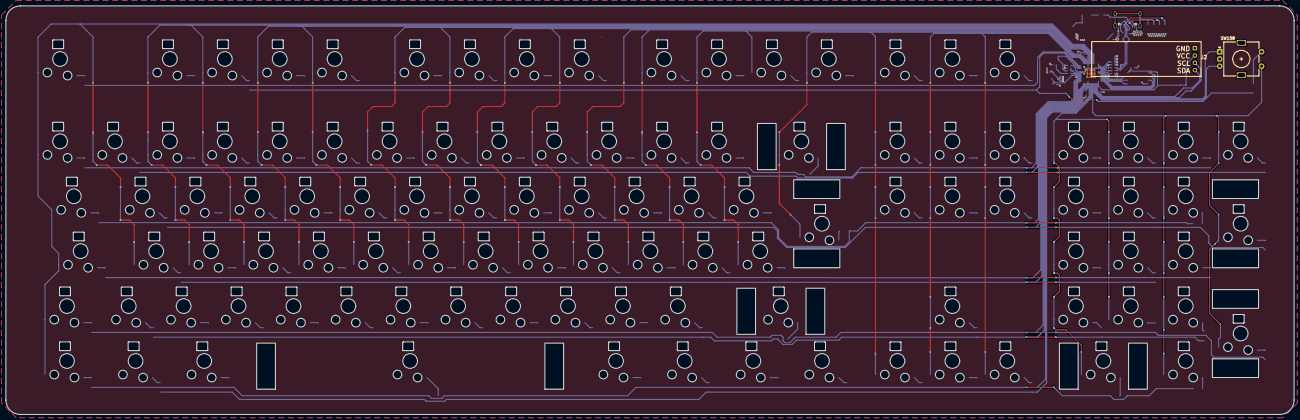
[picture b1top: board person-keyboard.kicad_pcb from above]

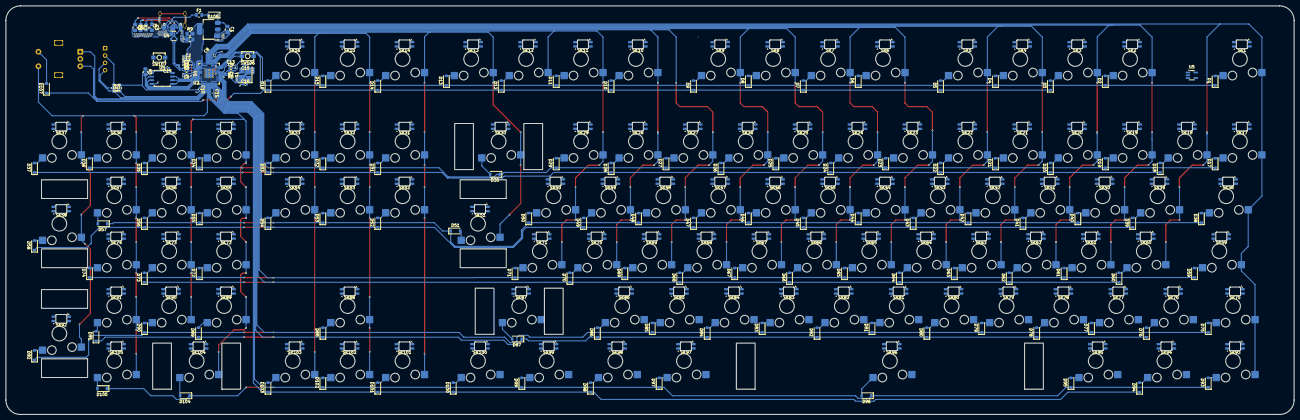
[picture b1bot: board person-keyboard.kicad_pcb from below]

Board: 2 copper layers, 446.9 x 141.7 mm, 357 parts (355 on the bottom side), 262 nets.

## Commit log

2025-07-15 Starting work
2025-07-16 Fixed key matrix, laid out LED matrix, started laying out microcontroller
2025-07-19 Added protection diode, reconsidered mcu position
2025-07-27 Routed microcontroller
2025-07-30 Started keyboard matrix, completed all rows, completed numpad columns
2025-08-16 Started Main matrix
2025-12-24 Completed Keyboard matrix, started LED chain
